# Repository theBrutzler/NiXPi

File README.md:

# RhapsodiePi
 Another RaspberryPi clone

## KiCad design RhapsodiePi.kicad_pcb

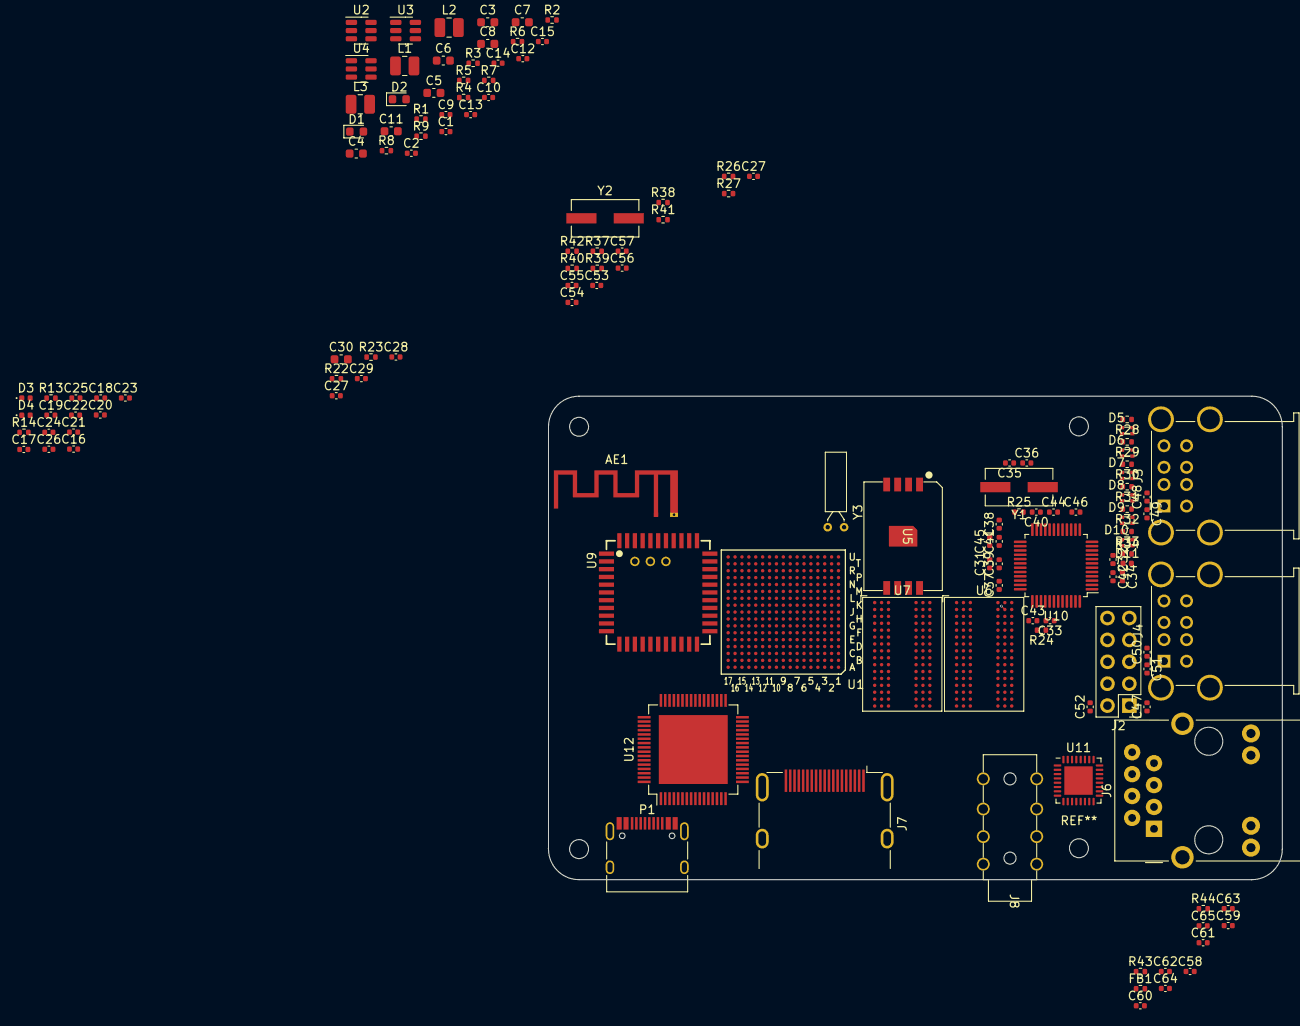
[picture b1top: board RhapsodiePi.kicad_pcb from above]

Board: 2 copper layers, 85.2 x 56.1 mm, 136 parts (1 on the bottom side), 189 nets.

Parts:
AE1: Antenna_Shield; Texas_SWRA117D_2.4GHz_Left
C1, C2, C9, C10, C12, C13, C14, C15, C17, C18, C19, C20, C21, C22, C23, C29, C33, C37, C39, C40, C41, C42, C43, C44, C45, C46, C58, C59, C62, C63, C64, C65: 100n; C_0402_1005Metric
C3, C4, C5, C6, C7, C8, C11, C30: 22µ; C_0603_1608Metric
C16, C24, C25, C26, C27, C27#2, C28, C31, C32, C34, C38, C47, C48, C49, C50, C51, C52, C60, C61: 1µ; C_0402_1005Metric
C35, C36: 20p; C_0402_1005Metric
C53, C54, C55, C56, C57: C; C_0402_1005Metric
D1, D2: D; D_0603_1608Metric
D3, D4, D11: LED; LED_0402_1005Metric
D5, D6, D7, D8, D9, D10: LED_Dual_LED; DUAL_LED_0603
FB1: FerriteBead; R_0402_1005Metric
J1: Micro_SD_Card_Det; HRS_DM3D-SF
J2: Conn_02x05_Odd_Even; PinHeader_2x05_P2.54mm_Vertical
J3, J4: USB_A_Stacked; USB_A_Wuerth_61400826021_Horizontal_Stacked
J6: RJ45_HR913550A
J7: HDMI_A; HDMI_A_Molex_208658-1001_Horizontal
J8: AudioJack4; AUDIO_3.5mm_PJ-313B6-B
L1, L2, L3: 2µ2; L_1008_2520Metric
P1: USB_C_Plug; USB_C_Receptacle_HRO_TYPE-C-31-M-12
R1: 50K; R_0402_1005Metric
R2: 30K; R_0402_1005Metric
R3: 450K; R_0402_1005Metric
R4, R6, R7, R8, R24, R38, R39, R41: 100K; R_0402_1005Metric
R5: 133K; R_0402_1005Metric
R9, R13, R14, R27, R28, R29, R30, R31, R32, R33, R34, R37, R40, R42, R43, R44: 1K; R_0402_1005Metric
R22, R23: 0R; R_0402_1005Metric
R25: 1MEG; R_0402_1005Metric
R26: 2K7; R_0402_1005Metric
U1: IMX6UL; IMX6UL_BGA289
U2, U3, U4: MT3420C-mt3420c; SOT-23-6
U5: MKDN0xxxCL; LGA-16_NAND
U6, U7: MT41K256M16TW; BGA-96_9.0x13.0mm_Layout2x3x16_P0.8mm
U9: AP6212
U10: FE2.1; LQFP-48_7x7mm_P0.5mm
U11: RTL8201F; QFN-32-1EP_5x5mm_P0.5mm_EP3.3x3.3mm
U12: TFP410PAP; HTQFP-64-1EP_10x10mm_P0.5mm_EP8x8mm
Y1: 12MHz; Crystal_SMD_ECS_CSM3X-2Pin_7.6x4.1mm
Y2: 24MHz; Crystal_SMD_ECS_CSM3X-2Pin_7.6x4.1mm
Y3: 32.768kHz; Crystal_C26-LF_D2.1mm_L6.5mm_Horizontal

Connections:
+1V2: C8.1, L3.2, R7.1
+1V4: C7.1, L2.2, R5.1, R9.1
+3V3: C6.1, C16.1, C24.1, C25.1, C26.1, C60.2, C62.2, FB1.1, J1.4 (VDD), L1.2, R3.1, R37.1, R39.1, R41.1, R43.1, U1.C4 (NVCC_SD1), U1.E7 (NVCC_NAND), U1.F13 (NVCC_ENET), U5.8 (VDD), U11.14 (DVDD33), U12.1 (DVDD), U12.12 (DVDD), U12.18 (PVDD), U12.23 (TVDD), U12.29 (TVDD), U12.33 (DVDD)
+5V: C3.1, C4.1, C5.1, C47.1, C48.1, C49.1, C50.1, C51.1, C52.1, J2.1, J2.2, J3.1 (VBUS1), J3.5 (VBUS2), J4.1 (VBUS1), J4.5 (VBUS2), P1.A4 (VBUS), P1.A9 (VBUS), P1.B4 (VBUS), P1.B9 (VBUS), R22.2, R23.2, U2.4 (IN), U3.1 (EN), U3.4 (IN), U4.4 (IN), U10.8 (VDD5), U10.41 (VBUSM)
/Display/HDMI_TX0n: J7.9 (D0-), U12.24 (TX0-)
/Display/HDMI_TX0p: J7.7 (D0+), U12.25 (TX0+)
/Display/HDMI_TX1n: J7.6 (D1-), U12.27 (TX1-)
/Display/HDMI_TX1p: J7.4 (D1+), U12.28 (TX1+)
/Display/HDMI_TX2n: J7.3 (D2-), U12.30 (TX2-)
/Display/HDMI_TX2p: J7.1 (D2+), U12.31 (TX2+)
/Display/HDMI_TXCn: J7.12 (CK-), U12.21 (TXC-)
/Display/HDMI_TXCp: J7.10 (CK+), U12.22 (TXC+)
/Display/LCD_CLK: U1.A8 (LCD_CLK), U12.57 (IDCK+)
/Display/LCD_DAT0: U1.B9 (LCD_DATA00), U12.63 (DATA0)
/Display/LCD_DAT1: U1.A9 (LCD_DATA01), U12.62 (DATA1)
/Display/LCD_DAT2: U1.E10 (LCD_DATA02), U12.61 (DATA2)
/Display/LCD_DAT3: U1.D10 (LCD_DATA03), U12.60 (DATA3)
/Display/LCD_DAT4: U1.C10 (LCD_DATA04), U12.59 (DATA4)
/Display/LCD_DAT5: U1.B10 (LCD_DATA05), U12.58 (DATA5)
/Display/LCD_DAT6: U1.A10 (LCD_DATA06), U12.55 (DATA6)
/Display/LCD_DAT7: U1.D11 (LCD_DATA07), U12.54 (DATA7)
/Display/LCD_DAT8: U1.B11 (LCD_DATA08), U12.53 (DATA8)
/Display/LCD_DAT9: U1.A11 (LCD_DATA09), U12.52 (DATA9)
/Display/LCD_DAT10: U1.E12 (LCD_DATA10), U12.51 (DATA10)
/Display/LCD_DAT11: U1.D12 (LCD_DATA11), U12.50 (DATA11)
/Display/LCD_DAT12: U1.C12 (LCD_DATA12), U12.47 (DATA12)
/Display/LCD_DAT13: U1.B12 (LCD_DATA13), U12.46 (DATA13)
/Display/LCD_DAT14: U1.A12 (LCD_DATA14), U12.45 (DATA14)
/Display/LCD_DAT15: U1.D13 (LCD_DATA15), U12.44 (DATA15)
/Display/LCD_DAT16: U1.C13 (LCD_DATA16), U12.43 (DATA16)
/Display/LCD_DAT17: U1.B13 (LCD_DATA17), U12.42 (DATA17)
/Display/LCD_DAT18: U1.A13 (LCD_DATA18), U12.41 (DATA18)
/Display/LCD_DAT19: U1.D14 (LCD_DATA19), U12.40 (DATA19)
/Display/LCD_DAT20: U1.C14 (LCD_DATA20), U12.39 (DATA20)
/Display/LCD_DAT21: U1.B14 (LCD_DATA21), U12.38 (DATA21)
/Display/LCD_DAT22: U1.A14 (LCD_DATA22), U12.37 (DATA22)
/Display/LCD_DAT23: U1.B16 (LCD_DATA23), U12.36 (DATA23)
/Display/LCD_EN: U1.B8 (LCD_ENABLE), U12.2 (DE)
/Display/LCD_HSYNC: U1.D9 (LCD_HSYNC), U12.4 (HSYNC)
/Display/LCD_RST: U1.E9 (LCD_RESET), U12.13 (ISEL/~RST)
/Display/LCD_VSYNC: U1.C9 (LCD_VSYNC), U12.5 (VSYNC)
/Memory/MMDC_A0: U1.L5 (DRAM_ADDR00), U6.N3 (A0), U7.N3 (A0)
/Memory/MMDC_A1: U1.H2 (DRAM_ADDR01), U6.P7 (A1), U7.P7 (A1)
/Memory/MMDC_A2: U1.K1 (DRAM_ADDR02), U6.P3 (A2), U7.P3 (A2)
/Memory/MMDC_A3: U1.M2 (DRAM_ADDR03), U6.N2 (A3), U7.N2 (A3)
/Memory/MMDC_A4: U1.K4 (DRAM_ADDR04), U6.P8 (A4), U7.P8 (A4)
/Memory/MMDC_A5: U1.L1 (DRAM_ADDR05), U6.P2 (A5), U7.P2 (A5)
/Memory/MMDC_A6: U1.G2 (DRAM_ADDR06), U6.R8 (A6), U7.R8 (A6)
/Memory/MMDC_A7: U1.H4 (DRAM_ADDR07), U6.R2 (A7), U7.R2 (A7)
/Memory/MMDC_A8: U1.J4 (DRAM_ADDR08), U6.T8 (A8), U7.T8 (A8)
/Memory/MMDC_A9: U1.L2 (DRAM_ADDR09), U6.R3 (A9), U7.R3 (A9)
/Memory/MMDC_A10: U1.M4 (DRAM_ADDR10), U6.L7 (A10/AP), U7.L7 (A10/AP)
/Memory/MMDC_A11: U1.K3 (DRAM_ADDR11), U6.R7 (A11), U7.R7 (A11)
/Memory/MMDC_A12: U1.L4 (DRAM_ADDR12), U6.N7 (A12/~BC), U7.N7 (A12/~BC)
/Memory/MMDC_A13: U1.H3 (DRAM_ADDR13), U6.T3 (A13), U7.T3 (A13)
/Memory/MMDC_A14: U1.G1 (DRAM_ADDR14), U6.T7 (A14), U7.T7 (A14)
/Memory/MMDC_BA0: U1.M1 (DRAM_SDBA0), U6.M2 (BA0), U7.M2 (BA0)
/Memory/MMDC_BA1: U1.H1 (DRAM_SDBA1), U6.N8 (BA1), U7.N8 (BA1)
/Memory/MMDC_BA2: U1.K2 (DRAM_SDBA2), U6.M3 (BA2), U7.M3 (BA2)
/Memory/MMDC_CKE0: U1.M3 (DRAM_SDCKE0), U6.K9 (CKE), U7.K9 (CKE)
/Memory/MMDC_CLKn: U1.P2 (DRAM_SDCLK0_N), U6.K7 (~CK), U7.K7 (~CK)
/Memory/MMDC_CLKp: U1.P1 (DRAM_SDCLK0_P), U6.J7 (CK), U7.J7 (CK)
/Memory/MMDC_D0: U1.T4 (DRAM_DATA00), U6.E3 (DQ0), U7.E3 (DQ0)
/Memory/MMDC_D1: U1.U6 (DRAM_DATA01), U6.F7 (DQ1), U7.F7 (DQ1)
/Memory/MMDC_D2: U1.T6 (DRAM_DATA02), U6.F2 (DQ2), U7.F2 (DQ2)
/Memory/MMDC_D3: U1.U7 (DRAM_DATA03), U6.F8 (DQ3), U7.F8 (DQ3)
/Memory/MMDC_D4: U1.U8 (DRAM_DATA04), U6.H3 (DQ4), U7.H3 (DQ4)
/Memory/MMDC_D5: U1.T8 (DRAM_DATA05), U6.H8 (DQ5), U7.H8 (DQ5)
/Memory/MMDC_D6: U1.T5 (DRAM_DATA06), U6.G2 (DQ6), U7.G2 (DQ6)
/Memory/MMDC_D7: U1.U4 (DRAM_DATA07), U6.H7 (DQ7), U7.H7 (DQ7)
/Memory/MMDC_D8: U1.U2 (DRAM_DATA08), U6.D7 (DQ8), U7.D7 (DQ8)
/Memory/MMDC_D9: U1.U3 (DRAM_DATA09), U6.C3 (DQ9), U7.C3 (DQ9)
/Memory/MMDC_D10: U1.U5 (DRAM_DATA10), U6.C8 (DQ10), U7.C8 (DQ10)
/Memory/MMDC_D11: U1.R4 (DRAM_DATA11), U6.C2 (DQ11), U7.C2 (DQ11)
/Memory/MMDC_D12: U1.P5 (DRAM_DATA12), U6.A7 (DQ12), U7.A7 (DQ12)
/Memory/MMDC_D13: U1.P3 (DRAM_DATA13), U6.A2 (DQ13), U7.A2 (DQ13)
/Memory/MMDC_D14: U1.R2 (DRAM_DATA14), U6.B8 (DQ14), U7.B8 (DQ14)
/Memory/MMDC_D15: U1.R1 (DRAM_DATA15), U6.A3 (DQ15), U7.A3 (DQ15)
/Memory/MMDC_ODT: U1.N1 (DRAM_ODT0), U6.K1 (ODT), U7.K1 (ODT)
/Memory/MMDC_~CAS: U1.J2 (DRAM_CAS_B), U6.K3 (~CAS), U7.K3 (~CAS)
/Memory/MMDC_~CS0: U1.N2 (DRAM_CS0_B), U6.L2 (~CS)
/Memory/MMDC_~CS1: U1.H5 (DRAM_CS1_B), U7.L2 (~CS)
/Memory/MMDC_~RAS: U1.M5 (DRAM_RAS_B), U6.J3 (~RAS), U7.J3 (~RAS)
/Memory/MMDC_~RST: U1.G4 (DRAM_RESET), U6.T2 (~RESET), U7.T2 (~RESET)
/Memory/MMDC_~WE: U1.J1 (DRAM_SDWE_B), U6.L3 (~WE), U7.L3 (~WE)
/Memory/NAND_CLK: U1.D8 (NAND_RE_B), U5.3 (CLK)
/Memory/NAND_CMD: U1.C8 (NAND_WE_B), U5.5 (CMD/DI)
/Memory/NAND_DAT0: U1.D7 (NAND_DATA00), U5.6 (DAT0/DO)
/Memory/NAND_DAT1: U1.B7 (NAND_DATA01), U5.7 (DAT1/RSV)
/Memory/NAND_DAT2: U1.A7 (NAND_DATA02), U5.1 (DAT2/RSV)
/Memory/NAND_DAT3: U1.D6 (NAND_DATA03), U5.2 (DAT3/~CS)
/Memory/SD1_CLK: J1.5 (CLK), U1.C1 (SD1_CLK)
/Memory/SD1_CMD: J1.3 (CMD), U1.C2 (SD1_CMD)
/Memory/SD1_DAT0: J1.7 (DAT0), U1.B3 (SD1_DATA0)
/Memory/SD1_DAT1: J1.8 (DAT1), U1.B2 (SD1_DATA1)
/Memory/SD1_DAT2: J1.1 (DAT2), U1.B1 (SD1_DATA2)
/Memory/SD1_DAT3: J1.2 (DAT3/CD), U1.A2 (SD1_DATA3)
/Network/ENET1_MDC: U1.C16 (ENET2_RX_DATA1), U11.22 (MDC)
/Network/ENET1_MDIO: U1.C17 (ENET2_RX_DATA0), U11.23 (MDIO)
/Network/ENET1_REFCLK: U1.E16 (ENET1_RX_EN), U11.32 (CKXTAL2)
/Network/ENET1_RXD0: U1.F16 (ENET1_RX_DATA0), U11.9 (RXD0)
/Network/ENET1_RXD1: U1.E17 (ENET1_RX_DATA1), U11.10 (RXD1)
/Network/ENET1_RXER: U1.D15 (ENET1_RX_ER), U11.28 (RXER)
/Network/ENET1_TXCLK: U1.F14 (ENET1_TX_CLK), U11.15 (TXC)
/Network/ENET1_TXD0: U1.E15 (ENET1_TX_DATA0), U11.16 (TXD0)
/Network/ENET1_TXD1: U1.E14 (ENET1_TX_DATA1), U11.17 (TXD1)
/Network/ENET1_TXEN: U1.F15 (ENET1_TX_EN), U11.20 (TXEN)
/Network/PHY_LED0: J6.L4 (LEDG_K), U11.24 (LED0/PHYAD0)
/Network/PHY_LED1: J6.L1 (LEDY_A), U11.25 (LED1/PHYAD1)
/Network/~PHYRST: U1.A15 (ENET2_TX_DATA0), U11.21 (PHYRSTB)
/USB/USB1_DN: P1.A7 (D-), U1.T15 (USB_OTG1_DN)
/USB/USB1_DP: P1.A6 (D+), U1.U15 (USB_OTG1_DP)
AGND2: AE1.2 (Shield), C1.2, C2.2, C3.2, C4.2, C5.2, C6.2, C7.2, C8.2, C9.1, C10.1, C11.2, C12.1, C13.2, C14.1, C15.1, C16.2, C17.2, C18.2, C19.2, C20.2, C21.2, C22.2, C23.2, C24.2, C25.2, C26.2, C27.2, C27#2.2, C28.2, C29.2, C30.2, C31.2, C32.2, C33.2, C34.2, C35.1, C36.1, C37.2, C38.2, C39.2, C40.2, C41.2, C42.2, C43.1, C44.2, C45.2, C46.2, C47.2, C48.2, C49.2, C50.2, C51.2, C52.2, C53.1, C54.1, C55.1, C56.1, C57.1, C58.2, C59.2, C60.1, C61.1, C62.1, C63.1, C64.1, C65.1, D3.1 (K), D4.1 (K), D11.1 (K), J1.6 (VSS), J1.10 (DET_A), J2.7, J2.8, J3.4 (GND1), J3.8 (GND2), J3.9 (Shield), J4.4 (GND1), J4.8 (GND2), J4.9 (Shield), J6.8 (GND), J6.SH (SHIELD), J7.2 (D2S), J7.5 (D1S), J7.8 (D0S), J7.11 (CKS), J7.17 (GND), J7.SH, P1.A1 (GND), P1.A12 (GND), P1.B1 (GND), P1.B12 (GND), P1.S1 (SHIELD), R4.2, R6.2, R8.2, R26.1, R27.2, R38.2, R40.2, R42.2, R44.1, U1.A1 (VSS), U1.A17 (VSS), U1.C3 (VSS), U1.C7 (VSS), U1.C11 (VSS), U1.C15 (VSS), U1.E8 (VSS), U1.E11 (VSS), U1.F6 (VSS), U1.F7 (VSS), U1.F8 (VSS), U1.F9 (VSS), U1.F10 (VSS), U1.F11 (VSS), U1.F12 (VSS), U1.G3 (VSS), U1.G5 (VSS), U1.G7 (VSS), U1.G12 (VSS), U1.G15 (VSS), U1.H7 (VSS), U1.H12 (VSS), U1.J5 (VSS), U1.J7 (VSS), U1.J12 (VSS), U1.K7 (VSS), U1.K12 (VSS), U1.L3 (VSS), U1.L7 (VSS), U1.L12 (VSS), U1.M7 (VSS), U1.M8 (VSS), U1.M9 (VSS), U1.M10 (VSS), U1.M11 (VSS), U1.M12 (NGND_KEL0), U1.N3 (VSS), U1.N5 (VSS), U1.R3 (VSS), U1.R5 (VSS), U1.R7 (VSS), U1.R11 (VSS), U1.R16 (VSS), U1.R17 (VSS), U1.T14 (VSS), U1.U1 (VSS), U1.U14 (VSS), U1.U17 (VSS), U2.2 (GND), U3.2 (GND), U4.2 (GND), U5.4 (GND), U6.A9 (VSS), U6.B1 (VSSQ), U6.B3 (VSS), U6.B9 (VSSQ), U6.D1 (VSSQ), U6.D8 (VSSQ), U6.E1 (VSS), U6.E2 (VSSQ), U6.E8 (VSSQ), U6.F9 (VSSQ), U6.G1 (VSSQ), U6.G8 (VSS), U6.G9 (VSSQ), U6.J2 (VSS), U6.J8 (VSS), U6.M1 (VSS), U6.M9 (VSS), U6.P1 (VSS), U6.P9 (VSS), U6.T1 (VSS), U6.T9 (VSS), U7.A9 (VSS), U7.B1 (VSSQ), U7.B3 (VSS), U7.B9 (VSSQ), U7.D1 (VSSQ), U7.D8 (VSSQ), U7.E1 (VSS), U7.E2 (VSSQ), U7.E8 (VSSQ), U7.F9 (VSSQ), U7.G1 (VSSQ), U7.G8 (VSS), U7.G9 (VSSQ), U7.J2 (VSS), U7.J8 (VSS), U7.M1 (VSS), U7.M9 (VSS), U7.P1 (VSS), U7.P9 (VSS), U7.T1 (VSS), U7.T9 (VSS), U9.1 (GND), U9.3 (GND), U9.20 (GND), U9.31 (GND), U9.33 (GND), U9.36 (GND), U10.10 (VSS), U10.24 (VSS_PLL), U10.39 (VSS), U11.33 (GND_PAD), U12.16 (DGND), U12.17 (PGND), U12.20 (TGND), U12.26 (TGND), U12.32 (TGND), U12.48 (DGND), U12.64 (DGND), U12.65 (EP), Y2.1
DP5+: J2.5, U10.33 (DP5)
DP5-: J2.3, U10.32 (DM5)
DP6+: J2.6, U10.35 (DP6)
DP6-: J2.4, U10.34 (DM6)
DRV: D5.2 (A2), D5.3 (K1), D6.2 (A2), D6.3 (K1), D7.2 (A2), D7.3 (K1), D8.2 (A2), D8.3 (K1), D9.2 (A2), D9.3 (K1), D10.2 (A2), D10.3 (K1), R34.1, U10.1 (DRV)
LED1: R28.2, U10.3 (LED[1])
LED2: R29.2, U10.4 (LED[2])
LED3: R30.2, U10.5 (LED[3])
LED4: R31.2, U10.7 (LED[4])
LED5: R32.2, U10.48 (LED[5])
LED6: R33.2, U10.47 (LED[6])
unnamed: AE1.1 (A), U9.2 (WL_BT_ANT)
unnamed: C1.1, D1.2 (A), R1.2, U2.1 (EN)
unnamed: C2.1, D2.2 (A), R2.2, U4.1 (EN)
unnamed: C9.2, C10.2, C11.1, C12.2, C13.1, C14.2, C15.2, U1.H9 (VDD_SOC_IN), U1.H10 (VDD_SOC_IN), U1.J9 (VDD_SOC_IN), U1.J10 (VDD_SOC_IN), U1.K9 (VDD_SOC_IN), U1.K10 (VDD_SOC_IN)
unnamed: C17.1, U1.P4 (DRAM_VREF)
unnamed: C18.1, C19.1, C20.1, C21.1, C22.1, C23.1, U1.G6 (NVCC_DRAM), U1.H6 (NVCC_DRAM), U1.J6 (NVCC_DRAM), U1.K6 (NVCC_DRAM), U1.L6 (NVCC_DRAM), U1.M6 (NVCC_DRAM)
unnamed: C27.1, C27#2.1, R22.1, U1.T12 (USB_OTG1_VBUS)
unnamed: C28.1, R23.1, U1.U12 (USB_OTG2_VBUS)
unnamed: C29.1, C30.1, U1.R12 (VDD_USB_CAP)
unnamed: C31.1, C32.1, C33.1, C37.1, C39.1, C41.1, C44.1, C46.1, R24.1, U10.9 (VDD33_O), U10.15 (VDD33), U10.20 (VDD33), U10.26 (VDD33), U10.31 (VDD33), U10.36 (VDD33), U10.42 (VDD33)
unnamed: C34.1, C38.1, C40.1, C42.1, C45.1, U10.6 (VDD18), U10.21 (VDD_PLL), U10.25 (VDD18_O), U10.28 (VDD18)
unnamed: C35.2, R25.1, U10.23 (CLK_OUT), Y1.2
unnamed: C36.2, R25.2, U10.22 (CLKIN), Y1.1
unnamed: C43.2, R24.2, U10.40 (XRST)
unnamed: C53.2, Y2.2
unnamed: C55.2, Y3.1
unnamed: C56.2, Y3.2
unnamed: C58.1, J6.2 (TCT)
unnamed: C59.1, J6.5 (RCT)
unnamed: C61.2, C63.2, FB1.2, U11.7 (AVDD33), U11.30 (AVDD33)
unnamed: C64.2, U11.29 (DVDD10OUT)
unnamed: C65.2, U11.2 (AVDD10OUT)
unnamed: D3.2 (A), R13.2
unnamed: D4.2 (A), R14.2
unnamed: D5.1 (A1), D5.4 (K2), R28.1
unnamed: D6.1 (A1), D6.4 (K2), R29.1
unnamed: D7.1 (A1), D7.4 (K2), R30.1
unnamed: D8.1 (A1), D8.4 (K2), R31.1
unnamed: D9.1 (A1), D9.4 (K2), R32.1
unnamed: D10.1 (A1), D10.4 (K2), R33.1
unnamed: D11.2 (A), R34.2
unnamed: J3.2 (D1-), U10.18 (DM1)
unnamed: J3.3 (D1+), U10.19 (DP1)
unnamed: J3.6 (D2-), U10.16 (DM2)
unnamed: J3.7 (D2+), U10.17 (DP2)
unnamed: J4.2 (D1-), U10.13 (DM3)
unnamed: J4.3 (D1+), U10.14 (DP3)
unnamed: J4.6 (D2-), U10.11 (DM4)
unnamed: J4.7 (D2+), U10.12 (DP4)
unnamed: J6.1 (TD+), U11.3 (MDI_0+)
unnamed: J6.3 (TD-), U11.4 (MDI_0-)
unnamed: J6.4 (RD+), U11.5 (MDI_1+)
unnamed: J6.6 (RD-), U11.6 (MDI_1-)
unnamed: J6.L2 (LEDY_K), R44.2
unnamed: J6.L3 (LEDG_A), R43.2
unnamed: L1.1, U2.3 (SW)
unnamed: L2.1, U3.3 (SW)
unnamed: L3.1, U4.3 (SW)
unnamed: R3.2, R4.1, U2.6 (FB)
unnamed: R5.2, R6.1, U3.6 (FB)
unnamed: R7.2, R8.1, U4.6 (FB)
unnamed: R13.1, U1.A5 (NAND_DATA07)
unnamed: R14.1, U1.A6 (NAND_DATA06)
unnamed: R26.2, U10.27 (REXT)
unnamed: R27.1, U10.46 (LED[7])
unnamed: R37.2, R38.1
unnamed: R39.2, R40.1
unnamed: R41.2, R42.1
unnamed: U1.T13 (USB_OTG2_DN), U10.29 (DMU)
unnamed: U1.U13 (USB_OTG2_DP), U10.30 (DPU)
unnamed: U6.A1 (VDDQ), U6.A8 (VDDQ), U6.C1 (VDDQ), U6.C9 (VDDQ), U6.D2 (VDDQ), U6.E9 (VDDQ), U6.F1 (VDDQ), U6.H2 (VDDQ), U6.H9 (VDDQ)
unnamed: U6.B2 (VDD), U6.D9 (VDD), U6.G7 (VDD), U6.K2 (VDD), U6.K8 (VDD), U6.N1 (VDD), U6.N9 (VDD), U6.R1 (VDD), U6.R9 (VDD)
unnamed: U7.A1 (VDDQ), U7.A8 (VDDQ), U7.C1 (VDDQ), U7.C9 (VDDQ), U7.D2 (VDDQ), U7.E9 (VDDQ), U7.F1 (VDDQ), U7.H2 (VDDQ), U7.H9 (VDDQ)
unnamed: U7.B2 (VDD), U7.D9 (VDD), U7.G7 (VDD), U7.K2 (VDD), U7.K8 (VDD), U7.N1 (VDD), U7.N9 (VDD), U7.R1 (VDD), U7.R9 (VDD)
PWR_EN: D1.1 (K), D2.1 (K), R1.1, R2.1, R9.2

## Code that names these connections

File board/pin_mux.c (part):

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  - {pin_num: R1, peripheral: MMDC, signal: 'mmdc_data, 15', pin_signal: DRAM_DATA15}
  - {pin_num: T7, peripheral: MMDC, signal: 'mmdc_dqm, 0', pin_signal: DRAM_DQM0}
  - {pin_num: T3, peripheral: MMDC, signal: 'mmdc_dqm, 1', pin_signal: DRAM_DQM1}
  - {pin_num: N1, peripheral: MMDC, signal: 'mmdc_odt, 0', pin_signal: DRAM_ODT0}
  - {pin_num: F1, peripheral: MMDC, signal: 'mmdc_odt, 1', pin_signal: DRAM_ODT1}
  - {pin_num: M5, peripheral: MMDC, signal: mmdc_ras_b, pin_signal: DRAM_RAS_B}
  - {pin_num: G4, peripheral: MMDC, signal: mmdc_reset, pin_signal: DRAM_RESET}
  - {pin_num: M1, peripheral: MMDC, signal: 'mmdc_sdba, 0', pin_signal: DRAM_SDBA0}
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  - {pin_num: B2, peripheral: uSDHC1, signal: 'usdhc_data, 1', pin_signal: SD1_DATA1}
  - {pin_num: B1, peripheral: uSDHC1, signal: 'usdhc_data, 2', pin_signal: SD1_DATA2}
  - {pin_num: A2, peripheral: uSDHC1, signal: 'usdhc_data, 3', pin_signal: SD1_DATA3}
  - {pin_num: C2, peripheral: uSDHC1, signal: usdhc_cmd, pin_signal: SD1_CMD}
  - {pin_num: C1, peripheral: uSDHC1, signal: usdhc_clk, pin_signal: SD1_CLK}
  - {pin_num: A3, peripheral: GPIO4, signal: 'gpio_io, 12', pin_signal: NAND_READY_B}
 * BE CAREFUL MODIFYING THIS COMMENT - IT IS YAML SETTINGS FOR TOOLS ***********
 */
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
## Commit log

2022-10-27 Initial Upload
    My inital upload of my own raspberrypi clone
2022-10-28 Update (Display)
2022-10-28 Update .gitignore
    Ignore all temporary KiCad files
2022-11-01 Add Audio
2022-11-07 New i.mx6 Version
2022-11-07 Need Rev Platinenmacher
    Commit 4 platinenmacher to review and finishing connections
2022-11-09 Display Update
2022-11-09 DDR: Review and connection of DDR3 chips
2022-11-09 Add current schmatic pdf
2022-12-20 update DDR
